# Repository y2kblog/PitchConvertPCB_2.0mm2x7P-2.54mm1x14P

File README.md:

# ピッチ変換基板(2.0mm 2×7P⇔2.54mm 1×14P)

## 概要
2.0mmピッチ2×7Pを2.54mmピッチ1×14Pに変換する基板です。

## 仕様
- ピンピッチ：2.0mm 2×7P ⇔ 2.54mm 1×14P
- 基板サイズ：10mm × 35.56mm
- 基板厚：1.6mm
- 基板色：緑
- 表面仕上げ：無鉛はんだ
- 両面スル―ホール
- 固定穴：30mmピッチ, φ3.2 × 2穴

## 販売  
[スイッチサイエンス委託販売ページ](https://www.switch-science.com/catalog/6586/)（ボックスヘッダ付）  
※大量注文や在庫に関する問い合わせは[こちら](mailto:info.y2kb@gmail.com)までご連絡ください。  

## 寸法

## License
MIT License, see `/LICENSE`.

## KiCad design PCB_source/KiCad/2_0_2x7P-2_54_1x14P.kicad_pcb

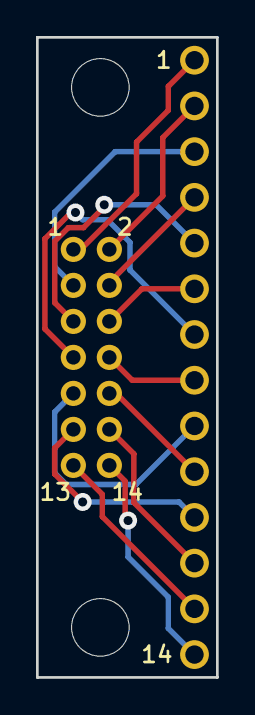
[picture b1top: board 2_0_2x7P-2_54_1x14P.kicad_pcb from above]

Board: 2 copper layers, 10.0 x 35.6 mm, 4 parts (0 on the bottom side), 14 nets.

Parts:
H1, H2: MountingHole; MountingHole_3.2mm_M3
J1: 2.00_2x7P; USER_DIL_2mm_7X2_NoSilk
J2: 2.54_1x14P; USER_SIL-14_NoSilk

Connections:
/1: J1.1, J2.1
/2: J1.2, J2.2
/3: J1.3, J2.3
/4: J1.4, J2.4
/5: J1.5, J2.5
/6: J1.6, J2.6
/7: J1.7, J2.7
/8: J1.8, J2.8
/9: J1.9, J2.9
/10: J1.10, J2.10
/11: J1.11, J2.11
/12: J1.12, J2.12
/13: J1.13, J2.13
/14: J1.14, J2.14

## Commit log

2020-09-06 add images
2020-09-12 Add link to sales page
